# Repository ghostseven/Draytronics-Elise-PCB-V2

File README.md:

# Draytronics-Elise-PCB-V2

An open source 65% mechanical keyboard, designed to be physically compatible with XD68. More info / kits / PCB designs available at https://www.draytronics.co.uk/elise

\

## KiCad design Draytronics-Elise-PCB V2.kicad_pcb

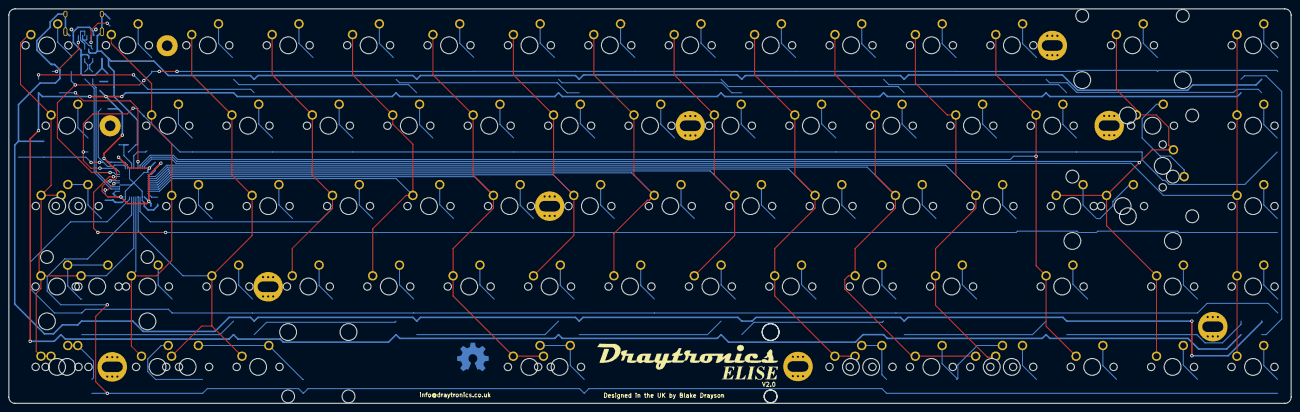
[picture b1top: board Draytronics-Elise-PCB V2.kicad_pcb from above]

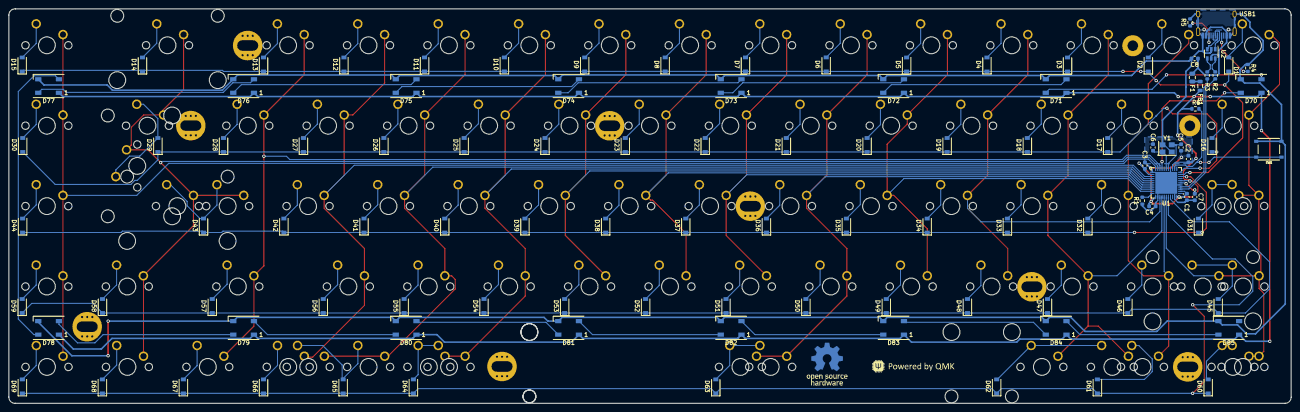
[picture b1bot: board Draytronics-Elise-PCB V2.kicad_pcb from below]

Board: 2 copper layers, 303.8 x 93.5 mm, 184 parts (106 on the bottom side), 122 nets.

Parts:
C1, C2, C3: 0.1u; C_0603_1608Metric
C4: 10u; C_0603_1608Metric
C5, C6: 22p; C_0603_1608Metric
C7: 1u; C_0603_1608Metric
C8: 4.7u; C_0603_1608Metric
D1, D2, D3, D4, D5, D6, D7, D8, D9, D10, D11, D12, D13, D14, D15, D16, D17, D18, D19, D20, D21, D22, D23, D24, D25, D26, D27, D28, D29, D30, D31, D32, D33, D34, D35, D36, D37, D38, D39, D40, D41, D42, D43, D44, D45, D46, D47, D48, D49, D50, D51, D52, D53, D54, D55, D56, D57, D58, D59, D60, D61, D62, D63, D64, D65, D66, D67, D68, D69: D_Small; D_SOD-123
D70, D71, D72, D73, D74, D75, D76, D77, D78, D79, D80, D81, D82, D83, D84, D85: WS2812B; LED_WS2812B_PLCC4_5.0x5.0mm_P3.2mm
F1: 1A; Fuse_0805_2012Metric
FB1: 100r @ 100 Mhz; L_0805_2012Metric
MX1, MX2, MX3, MX4, MX5, MX6, MX7, MX8, MX9, MX10, MX11, MX12, MX13, MX15, MX17, MX18, MX19, MX20, MX21, MX22, MX23, MX24, MX25, MX26, MX27, MX28, MX30, MX34, MX35, MX36, MX37, MX38, MX39, MX40, MX41, MX42, MX43, MX44, MX47, MX50, MX51, MX52, MX53, MX54, MX55, MX56, MX57, MX58, MX59, MX60, MX62, MX63, MX71, MX72, MX73: MX-NoLED; MXOnly-1U-NoLED
MX14: 2U; MXOnly-2U-NoLED
MX16, MX29, MX74, MX75, MX77, MX78: 1.5U; MXOnly-1.5U-NoLED
MX31: ISO; MXOnly-ISO-ROTATED-ReversedStabilizers-NoLED
MX32, MX48, MX64, MX65, MX66: 1.25U; MXOnly-1.25U-NoLED
MX33, MX61: 1.75U; MXOnly-1.75U-NoLED
MX45, MX49: 2.25U; MXOnly-2.25U-NoLED
MX46, MX68, MX69, MX70: 1U; MXOnly-1U-NoLED
MX67: 6.25U; MXOnly-6.25U-ReversedStabilizers-NoLED
MX76: 7U; MXOnly-7U-ReversedStabilizers-NoLED
R1, R6: 10k; R_0603_1608Metric
R2, R3: 22r; R_0603_1608Metric
R4, R5: 5.1k; R_0603_1608Metric
SW1: SW_Push; TS-1187A-B-A-B
U1: ATmega32U4-MU; QFN-44-1EP_7x7mm_P0.5mm_EP5.2x5.2mm
U2: USBLC6-2SC6; SOT-23-6
USB1: HRO-TYPE-C-31-M-12; HRO-TYPE-C-31-M-12-Assembly
Y1: 16MHz; Crystal_SMD_3225-4Pin_3.2x2.5mm

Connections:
+5V: C1.1, C2.1, C3.1, C4.1, D70.1, D71.1, D72.1, D73.1, D74.1, D75.1, D76.1, D77.1, D78.1, D79.1, D80.1, D81.1, D82.1, D83.1, D84.1, D85.1, FB1.2, R6.1, U1.2, U1.7, U1.14, U1.24, U1.34, U1.44
/ESD_D+: R3.2, U2.4
/ESD_D-: R2.2, U2.6
COL0: MX1.1, MX16.1, MX32.1, MX33.1, MX48.1, MX49.1, MX64.1, MX74.1, U1.39
COL1: MX2.1, MX17.1, MX34.1, MX50.1, MX65.1, U1.38
COL2: MX3.1, MX18.1, MX35.1, MX51.1, MX66.1, MX75.1, U1.37
COL3: MX4.1, MX19.1, MX36.1, MX52.1, U1.36
COL4: MX5.1, MX20.1, MX37.1, MX53.1, U1.32
COL5: MX6.1, MX21.1, MX38.1, MX54.1, MX67.1, MX76.1, U1.31
COL6: MX7.1, MX22.1, MX39.1, MX55.1, U1.30
COL7: MX8.1, MX23.1, MX40.1, MX56.1, U1.29
COL8: MX9.1, MX24.1, MX41.1, MX57.1, U1.28
COL9: MX10.1, MX25.1, MX42.1, MX58.1, MX68.1, MX77.1, U1.27
COL10: MX11.1, MX26.1, MX43.1, MX59.1, MX69.1, MX78.1, U1.26
COL11: MX12.1, MX27.1, MX44.1, MX60.1, MX70.1, U1.25
COL12: MX13.1, MX28.1, MX61.1, MX71.1, U1.20
COL13: MX14.1, MX29.1, MX31.1, MX45.1, MX46.1, MX62.1, MX72.1, U1.21
COL14: MX15.1, MX30.1, MX47.1, MX63.1, MX73.1, U1.22
D+: R3.1, U1.4
D-: R2.1, U1.3
DBus+: U2.3, USB1.6, USB1.8
DBus-: U2.1, USB1.5, USB1.7
GND: C1.2, C2.2, C3.2, C4.2, C5.1, C6.1, C7.2, C8.2, D70.3, D71.3, D72.3, D73.3, D74.3, D75.3, D76.3, D77.3, D78.3, D79.3, D80.3, D81.3, D82.3, D83.3, D84.3, D85.3, R1.1, R4.1, R5.1, SW1.1, U1.5, U1.15, U1.23, U1.35, U1.43, U1.45, U2.2, USB1.1, USB1.12, USB1.13, Y1.2, Y1.4
unnamed: C7.1, U1.6
unnamed: D1.2, MX1.2
unnamed: D2.2, MX2.2
unnamed: D3.2, MX3.2
unnamed: D4.2, MX4.2
unnamed: D5.2, MX5.2
unnamed: D6.2, MX6.2
unnamed: D7.2, MX7.2
unnamed: D8.2, MX8.2
unnamed: D9.2, MX9.2
unnamed: D10.2, MX10.2
unnamed: D11.2, MX11.2
unnamed: D12.2, MX12.2
unnamed: D13.2, MX13.2
unnamed: D14.2, MX14.2
unnamed: D15.2, MX15.2
unnamed: D16.2, MX16.2
unnamed: D17.2, MX17.2
unnamed: D18.2, MX18.2
unnamed: D19.2, MX19.2
unnamed: D20.2, MX20.2
unnamed: D21.2, MX21.2
unnamed: D22.2, MX22.2
unnamed: D23.2, MX23.2
unnamed: D24.2, MX24.2
unnamed: D25.2, MX25.2
unnamed: D26.2, MX26.2
unnamed: D27.2, MX27.2
unnamed: D28.2, MX28.2
unnamed: D29.2, MX29.2, MX31.2
unnamed: D30.2, MX30.2
unnamed: D31.2, MX32.2, MX33.2
unnamed: D32.2, MX34.2
unnamed: D33.2, MX35.2
unnamed: D34.2, MX36.2
unnamed: D35.2, MX37.2
unnamed: D36.2, MX38.2
unnamed: D37.2, MX39.2
unnamed: D38.2, MX40.2
unnamed: D39.2, MX41.2
unnamed: D40.2, MX42.2
unnamed: D41.2, MX43.2
unnamed: D42.2, MX44.2
unnamed: D43.2, MX45.2, MX46.2
unnamed: D44.2, MX47.2
unnamed: D45.2, MX48.2, MX49.2
unnamed: D46.2, MX50.2
unnamed: D47.2, MX51.2
unnamed: D48.2, MX52.2
unnamed: D49.2, MX53.2
unnamed: D50.2, MX54.2
unnamed: D51.2, MX55.2
unnamed: D52.2, MX56.2
unnamed: D53.2, MX57.2
unnamed: D54.2, MX58.2
unnamed: D55.2, MX59.2
unnamed: D56.2, MX60.2
unnamed: D57.2, MX61.2
unnamed: D58.2, MX62.2
unnamed: D59.2, MX63.2
unnamed: D60.2, MX64.2, MX74.2
unnamed: D61.2, MX65.2
unnamed: D62.2, MX66.2, MX75.2
unnamed: D63.2, MX67.2, MX76.2
unnamed: D64.2, MX68.2, MX77.2
unnamed: D65.2, MX69.2, MX78.2
unnamed: D66.2, MX70.2
unnamed: D67.2, MX71.2
unnamed: D68.2, MX72.2
unnamed: D69.2, MX73.2
unnamed: D70.2, D71.4
unnamed: D71.2, D72.4
unnamed: D72.2, D73.4
unnamed: D73.2, D74.4
unnamed: D74.2, D75.4
unnamed: D75.2, D76.4
unnamed: D76.2, D77.4
unnamed: D77.2, D78.4
unnamed: D78.2, D79.4
unnamed: D79.2, D80.4
unnamed: D80.2, D81.4
unnamed: D81.2, D82.4
unnamed: D82.2, D83.4
unnamed: D83.2, D84.4
unnamed: D84.2, D85.4
unnamed: F1.2, FB1.1
unnamed: R1.2, U1.33
unnamed: R4.2, USB1.4
unnamed: R5.2, USB1.10
RESET: R6.2, SW1.2, U1.13
RGBLED: D70.4, U1.19
ROW0: D1.1, D2.1, D3.1, D4.1, D5.1, D6.1, D7.1, D8.1, D9.1, D10.1, D11.1, D12.1, D13.1, D14.1, D15.1, U1.10
ROW1: D16.1, D17.1, D18.1, D19.1, D20.1, D21.1, D22.1, D23.1, D24.1, D25.1, D26.1, D27.1, D28.1, D29.1, D30.1, U1.11
ROW2: D31.1, D32.1, D33.1, D34.1, D35.1, D36.1, D37.1, D38.1, D39.1, D40.1, D41.1, D42.1, D43.1, D44.1, U1.9
ROW3: D45.1, D46.1, D47.1, D48.1, D49.1, D50.1, D51.1, D52.1, D53.1, D54.1, D55.1, D56.1, D57.1, D58.1, D59.1, U1.41
ROW4: D60.1, D61.1, D62.1, D63.1, D64.1, D65.1, D66.1, D67.1, D68.1, D69.1, U1.40
VCC: C8.1, F1.1, U2.5, USB1.2, USB1.11
XTAL1: C6.2, U1.17, Y1.1
XTAL2: C5.2, U1.16, Y1.3

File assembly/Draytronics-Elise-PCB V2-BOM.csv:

Reference, Quantity, Value, Footprint, Datasheet, LCSC Part #
C1 C2 C3 ,3,"0.1u","Capacitor_SMD:C_0603_1608Metric","~","C14663"
C4 ,1,"10u","Capacitor_SMD:C_0603_1608Metric","~","C19702"
C5 C6 ,2,"22p","Capacitor_SMD:C_0603_1608Metric","~","C1653"
C7 ,1,"1u","Capacitor_SMD:C_0603_1608Metric","~","C15849"
C8 ,1,"4.7u","Capacitor_SMD:C_0603_1608Metric","~","C19666"
D1 D2 D3 D4 D5 D6 D7 D8 D9 D10 D11 D12 D13 D14 D15 D16 D17 D18 D19 D20 D21 D22 D23 D24 D25 D26 D27 D28 D29 D30 D31 D32 D33 D34 D35 D36 D37 D38 D39 D40 D41 D42 D43 D44 D45 D46 D47 D48 D49 D50 D51 D52 D53 D54 D55 D56 D57 D58 D59 D60 D61 D62 D63 D64 D65 D66 D67 D68 D69 ,69,"D_Small","Diode_SMD:D_SOD-123","~","C81598"
D70 D71 D72 D73 D74 D75 D76 D77 D78 D79 D80 D81 D82 D83 D84 D85 ,16,"WS2812B","LED_SMD:LED_WS2812B_PLCC4_5.0x5.0mm_P3.2mm","https://cdn-shop.adafruit.com/datasheets/WS2812B.pdf","C114586"
F1 ,1,"1A","Fuse:Fuse_0805_2012Metric","~","C261942"
FB1 ,1,"100r @ 100 Mhz","Inductor_SMD:L_0805_2012Metric","~","C1015"
MX1 MX2 MX3 MX4 MX5 MX6 MX7 MX8 MX9 MX10 MX11 MX12 MX13 MX15 MX17 MX18 MX19 MX20 MX21 MX22 MX23 MX24 MX25 MX26 MX27 MX28 MX30 MX34 MX35 MX36 MX37 MX38 MX39 MX40 MX41 MX42 MX43 MX44 MX47 MX50 MX51 MX52 MX53 MX54 MX55 MX56 MX57 MX58 MX59 MX60 MX62 MX63 MX71 MX72 MX73 ,55,"MX-NoLED","MX_Only:MXOnly-1U-NoLED",""
MX14 ,1,"2U","MX_Only:MXOnly-2U-NoLED",""
MX16 MX29 MX74 MX75 MX77 MX78 ,6,"1.5U","MX_Only:MXOnly-1.5U-NoLED",""
MX31 ,1,"ISO","MX_Only:MXOnly-ISO-ROTATED-ReversedStabilizers-NoLED",""
MX32 MX48 MX64 MX65 MX66 ,5,"1.25U","MX_Only:MXOnly-1.25U-NoLED",""
MX33 MX61 ,2,"1.75U","MX_Only:MXOnly-1.75U-NoLED",""
MX46 MX68 MX69 MX70 ,4,"1U","MX_Only:MXOnly-1U-NoLED",""
MX45 MX49 ,2,"2.25U","MX_Only:MXOnly-2.25U-NoLED",""
MX67 ,1,"6.25U","MX_Only:MXOnly-6.25U-ReversedStabilizers-NoLED",""
MX76 ,1,"7U","MX_Only:MXOnly-7U-ReversedStabilizers-NoLED",""
R1 R6 ,2,"10k","Resistor_SMD:R_0603_1608Metric","~","C25804"
R2 R3 ,2,"22r","Resistor_SMD:R_0603_1608Metric","~","C23345"
R4 R5 ,2,"5.1k","Resistor_SMD:R_0603_1608Metric","~","C23186"
SW1 ,1,"SW_Push","Draytronics Footprints:TS-1187A-B-A-B","~","C318884"
U1 ,1,"ATmega32U4-MU","Package_DFN_QFN:QFN-44-1EP_7x7mm_P0.5mm_EP5.2x5.2mm","http://ww1.microchip.com/downloads/en/DeviceDoc/Atmel-7766-8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","C45874"
U2 ,1,"USBLC6-2SC6","Package_TO_SOT_SMD:SOT-23-6","https://www.st.com/resource/en/datasheet/usblc6-2.pdf","C7519"
USB1 ,1,"HRO-TYPE-C-31-M-12","Type-C:HRO-TYPE-C-31-M-12-Assembly","","C165948"
Y1 ,1,"16MHz","Crystal:Crystal_SMD_3225-4Pin_3.2x2.5mm","~","C13738"
